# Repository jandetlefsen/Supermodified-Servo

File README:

Eagle files for "Supermodified" Servos. 
These are servos with full digital control. 
Advantages:
- 4096 positions / 360 degrees
- Bus interfaces (I2C, RS485)
- Velocity feedback
- Continuous rotation
- Current feedback

http://letsmakerobots.com/node/18615
http://www.01mech.com/supermodified

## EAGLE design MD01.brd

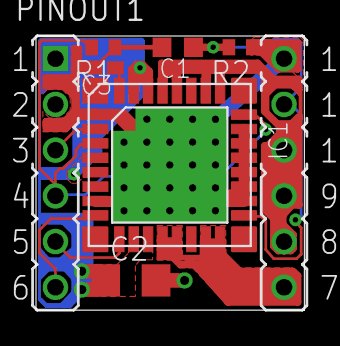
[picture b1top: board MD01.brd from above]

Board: 2 copper layers, 14.9 x 15.2 mm, 7 parts (0 on the bottom side), 10 nets.

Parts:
C1: C0603K
C2: C3216
C3: C0402K
IC1: MC33887; PGFN-36
PINOUT1: SMSPINS
R1, R2: R0402

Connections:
!FAULT: IC1.9, PINOUT1.6
CURR: C1.1, IC1.20, PINOUT1.11, R2.2
GND: C1.2, C2.2, C3.2, IC1.2, IC1.8, IC1.21, IC1.22, IC1.23, IC1.24, IC1.25, IC1.26, IC1.TH1, IC1.TH2, IC1.TH3, IC1.TH4, IC1.TH5, IC1.TH6, IC1.TH7, IC1.TH8, IC1.TH9, IC1.TH10, IC1.TH11, IC1.TH12, IC1.TH13, IC1.TH14, IC1.TH15, IC1.TH16, IC1.TH17, IC1.TH18, IC1.TH19, IC1.TH20, IC1.TH21, IC1.TH22, IC1.TH23, IC1.TH24, PINOUT1.12, R1.1, R2.1
MOT+: IC1.14, IC1.15, IC1.17, IC1.18, PINOUT1.7
MOT-: IC1.29, IC1.30, IC1.32, IC1.33, PINOUT1.8, PINOUT1.9, PINOUT1.10
MOT_EN: IC1.4, IC1.27, PINOUT1.4, R1.2
unnamed: C3.1, IC1.36
PWM1: IC1.11, PINOUT1.5
PWM2: IC1.3, PINOUT1.3
VIN: C2.1, IC1.5, IC1.6, IC1.12, IC1.13, IC1.34, IC1.35, PINOUT1.1

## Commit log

2011-05-23 added files
2011-05-23 added gitignore
2011-05-23 included render
2011-05-23 added README content
2013-03-07 Increased polygon widths from 0 to 6 mils.
